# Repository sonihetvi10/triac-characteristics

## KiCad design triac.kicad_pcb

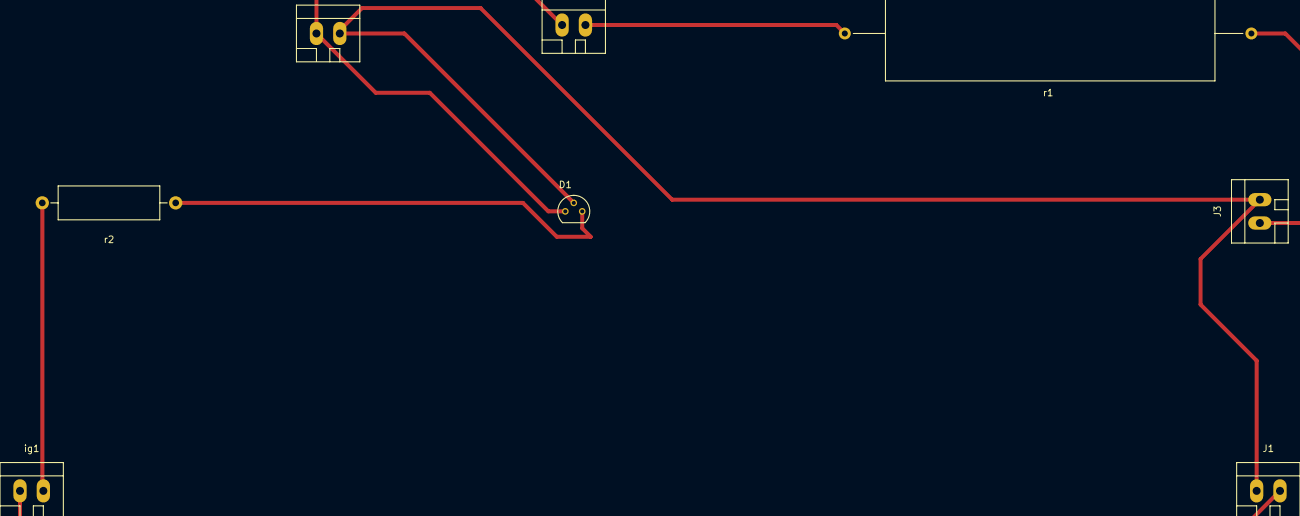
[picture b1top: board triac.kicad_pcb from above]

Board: 2 copper layers, 8 parts (0 on the bottom side), 7 nets.

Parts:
D1: Q_TRIAC_AAG; TO-92_Molded_Narrow
J1, J2, J3, J4: Conn_01x02; WAGO_734_2pin_Straight_RuggedPads
ig1: Conn_01x02; WAGO_734_2pin_Straight_RuggedPads
r1: 1k; Resistor_Ceramic_Horizontal_L50mm-W14mm-H13mm-p60mm
r2: 1k; Resistor_Horizontal_RM20mm

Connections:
/gnd: D1.2, J1.1, J3.2, J4.2
/v1: D1.1, J2.1, J4.1
unnamed: D1.3, r2.1
unnamed: J1.2, ig1.1
unnamed: J2.2, r1.2
unnamed: J3.1, r1.1
unnamed: ig1.2, r2.2
